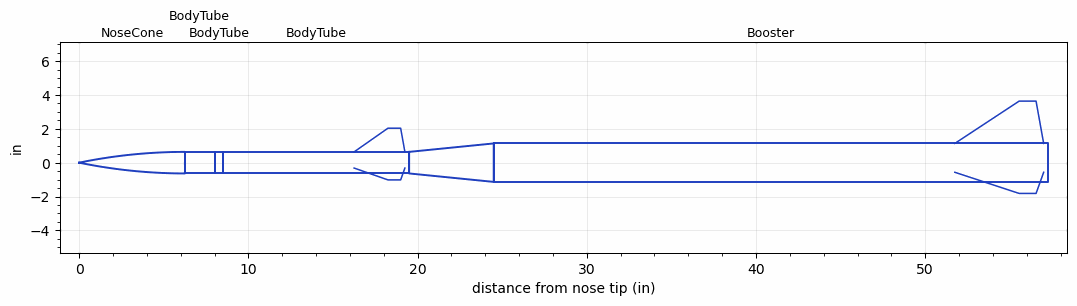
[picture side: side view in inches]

<RASAeroDocument>
 <FileVersion>2</FileVersion>
 <RocketDesign>
  <NoseCone>
   <Length>6.25</Length>
   <Diameter>1.274</Diameter>
   <Shape>Tangent Ogive</Shape>
   <Location>0</Location>
  </NoseCone>
  <BodyTube>
   <Length>1.75</Length>
   <Diameter>1.274</Diameter>
   <Location>6.25</Location>
  </BodyTube>
  <BodyTube>
   <Length>0.5</Length>
   <Diameter>1.274</Diameter>
   <Location>8</Location>
  </BodyTube>
  <BodyTube>
   <Length>11</Length>
   <Diameter>1.274</Diameter>
   <Location>8.5</Location>
   <Fin>
    <Count>3</Count>
    <Chord>3</Chord>
    <Span>1.4</Span>
    <SweepDistance>2</SweepDistance>
    <TipChord>0.75</TipChord>
    <Thickness>0.125</Thickness>
    <LERadius>0.05</LERadius>
    <Location>3.25</Location>
    <AirfoilSection>Hexagonal</AirfoilSection>
    <FX1>0.25</FX1>
    <FX3>0.25</FX3>
   </Fin>
  </BodyTube>
  <Booster>
   <Length>32.7499</Length>
   <Diameter>2.274</Diameter>
   <InsideDiameter>1.274</InsideDiameter>
   <Location>19.5</Location>
   <ShoulderLength>5</ShoulderLength>
   <Fin>
    <Count>3</Count>
    <Chord>5.25</Chord>
    <Span>2.5</Span>
    <SweepDistance>3.8</SweepDistance>
    <TipChord>1</TipChord>
    <Thickness>0.125</Thickness>
    <LERadius>0.05</LERadius>
    <Location>5.5</Location>
    <AirfoilSection>Hexagonal</AirfoilSection>
    <FX1>0.25</FX1>
    <FX3>0.25</FX3>
   </Fin>
  </Booster>
  <Surface>Camouflage Paint</Surface>
  <ModifiedBarrowman>True</ModifiedBarrowman>
  <Turbulence>True</Turbulence>
  <UseBooster1>True</UseBooster1>
  <UseBooster2>False</UseBooster2>
 </RocketDesign>
 <LaunchSite>
  <Altitude>850</Altitude>
  <Pressure>29.08</Pressure>
  <RodAngle>1</RodAngle>
  <RodLength>72</RodLength>
  <Temperature>70</Temperature>
  <WindSpeed>9</WindSpeed>
 </LaunchSite>
 <Recovery>
  <Altitude1>700</Altitude1>
  <Altitude2>656.168</Altitude2>
  <DeviceType1>Parachute</DeviceType1>
  <DeviceType2>Parachute</DeviceType2>
  <Event1>True</Event1>
  <Event2>True</Event2>
  <Size1>24</Size1>
  <Size2>18</Size2>
  <EventType1>Altitude</EventType1>
  <EventType2>Apogee</EventType2>
  <CD1>0.5</CD1>
  <CD2>0</CD2>
 </Recovery>
 <SimulationList>
  <Simulation>
   <SustainerEngine>Dart  (NoThrust)</SustainerEngine>
   <SustainerLaunchWt>1.12</SustainerLaunchWt>
   <SustainerCG>12.35</SustainerCG>
   <SustainerIgnitionDelay>0</SustainerIgnitionDelay>
   <Booster1Engine>J540R  (AT)</Booster1Engine>
   <Booster1LaunchWt>5.34</Booster1LaunchWt>
   <Booster1SeparationDelay>0</Booster1SeparationDelay>
   <Booster1IgnitionDelay>0</Booster1IgnitionDelay>
   <Booster1CG>36.8</Booster1CG>
   <Booster1NozzleDiameter>0.5</Booster1NozzleDiameter>
   <IncludeBooster1>True</IncludeBooster1>
   <Booster2Delay>0</Booster2Delay>
   <IncludeBooster2>False</IncludeBooster2>
   <TimetoApogee>22.70037</TimetoApogee>
   <MaxAltitude>11095.36</MaxAltitude>
   <MaxVelocity>1392.561</MaxVelocity>
  </Simulation>
 </SimulationList>
</RASAeroDocument>
